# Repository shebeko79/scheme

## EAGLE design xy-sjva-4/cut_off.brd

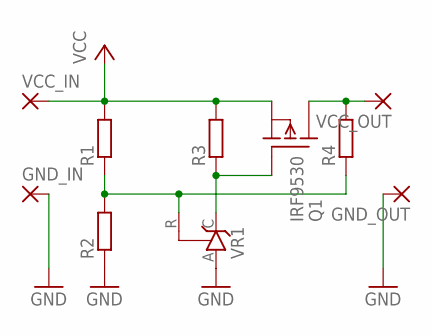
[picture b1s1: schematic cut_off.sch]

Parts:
GND_IN: 2,15/1,0
GND_OUT: 2,15/1,0
Q1: IRF9530; TO220
R1, R2, R3, R4: R-EU_R0805; R0805
VCC_IN: 2,15/1,0
VCC_OUT: 2,15/1,0
VR1: TL431CLP; TO92-CLP

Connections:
GND: GND_IN.1, GND_OUT.1, R2.1, VR1.A
unnamed: R1.1, R2.2, R4.1, VR1.R
unnamed: Q1.1 (G), R3.1, VR1.C
VCC: Q1.3 (S), R1.2, R3.2, VCC_IN.1
VCC_OUT: Q1.2 (D), R4.2, VCC_OUT.1

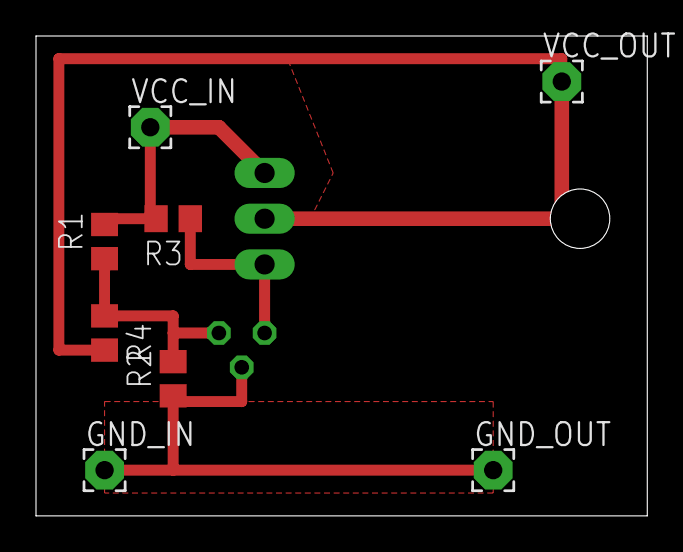
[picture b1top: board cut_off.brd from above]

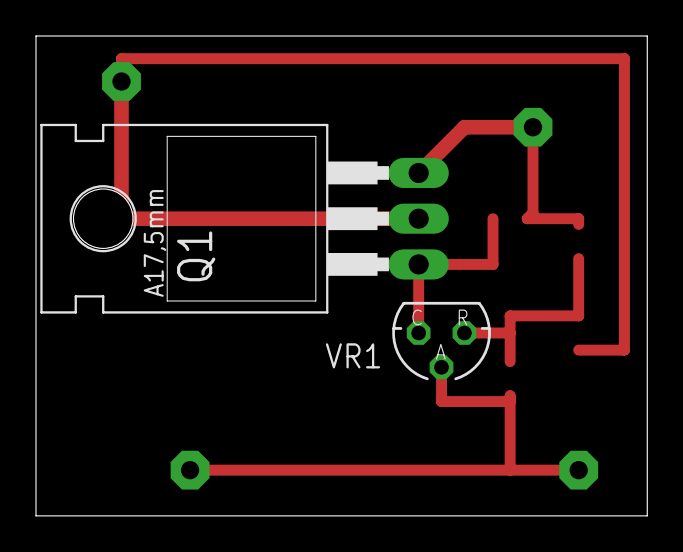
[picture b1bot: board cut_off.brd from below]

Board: 2 copper layers, 34.0 x 26.7 mm, 10 parts (2 on the bottom side), 5 nets.

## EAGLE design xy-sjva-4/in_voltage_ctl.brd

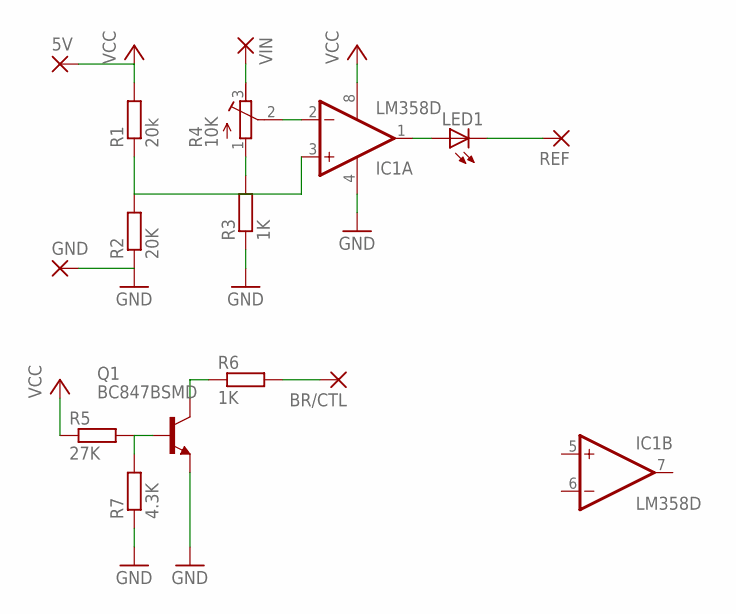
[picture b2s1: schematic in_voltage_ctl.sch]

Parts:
5V: SMD2; SMD1,27-2,54
BR/CTL: SMD2; SMD1,27-2,54
GND: SMD2; SMD1,27-2,54
IC1: LM358D; SO08
LED1: LEDSML0805; SML0805
Q1: BC847BSMD; SOT23
R1: 20k; R0805
R2: 20K; R0805
R3, R6: 1K; R0805
R4: 10K; RTRIM3296W
R5: 27K; R0805
R7: 4.3K; R0805
REF: SMD2; SMD1,27-2,54
VIN: SMD2; SMD1,27-2,54

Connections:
GND: GND.1, IC1.4 (V-), Q1.2 (E), R2.1, R3.1, R7.1
unnamed: IC1.3 (+IN), R1.1, R2.2
unnamed: IC1.1 (OUT), LED1.A
unnamed: LED1.C, REF.1
unnamed: Q1.1 (B), R5.2, R7.2
unnamed: Q1.3 (C), R6.1
unnamed: BR/CTL.1, R6.2
REF: IC1.2 (-IN), R4.2 (S)
REF_GND: R3.2, R4.1 (A)
VCC: 5V.1, IC1.8 (V+), R1.2, R5.1
VIN: R4.3 (E), VIN.1

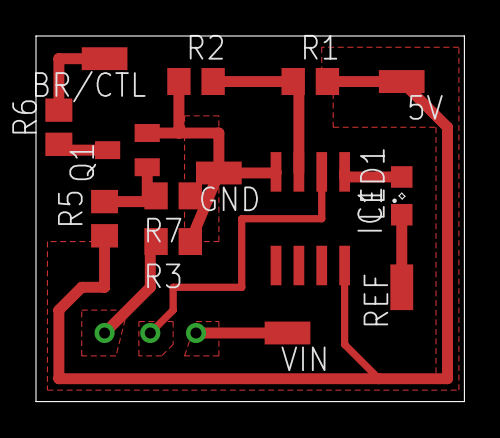
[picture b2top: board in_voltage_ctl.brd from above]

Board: 2 copper layers, 23.8 x 20.3 mm, 15 parts (1 on the bottom side), 11 nets.

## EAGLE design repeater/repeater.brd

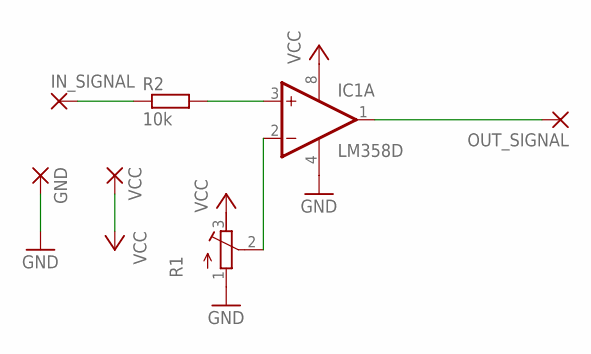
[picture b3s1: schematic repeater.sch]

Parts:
GND: SMD5; SMD2,54-5,08
IC1: LM358D; SO08
IN_SIGNAL: SMD5; SMD2,54-5,08
OUT_SIGNAL: SMD5; SMD2,54-5,08
R1: R-TRIMM3296W; RTRIM3296W
R2: 10k; R0805
VCC: SMD5; SMD2,54-5,08

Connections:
GND: GND.1, IC1.4 (V-), R1.1 (A)
unnamed: IC1.2 (-IN), R1.2 (S)
unnamed: IC1.3 (+IN), R2.2
unnamed: IN_SIGNAL.1, R2.1
unnamed: IC1.1 (OUT), OUT_SIGNAL.1
VCC: IC1.8 (V+), R1.3 (E), VCC.1

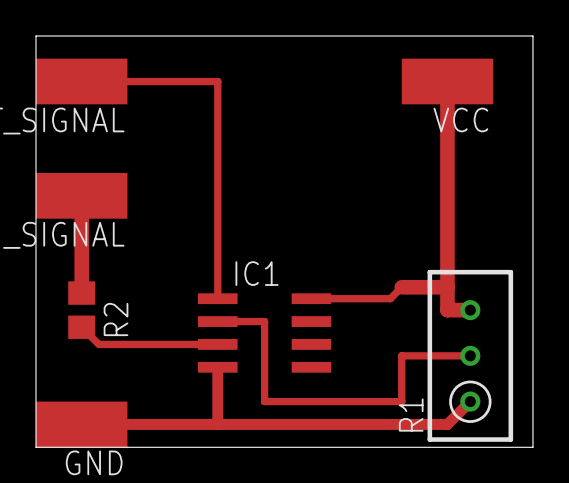
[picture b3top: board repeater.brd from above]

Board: 2 copper layers, 27.6 x 22.9 mm, 7 parts (0 on the bottom side), 6 nets.

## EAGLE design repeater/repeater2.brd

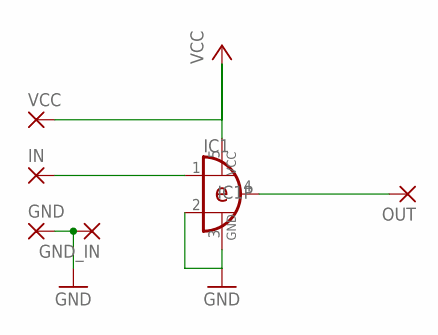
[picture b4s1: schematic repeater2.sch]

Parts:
GND: SMD2; SMD1,27-2,54
GND_IN: SMD2; SMD1,27-2,54
IC1: 74AHC1G86DCK; SC70-5
IN: SMD2; SMD1,27-2,54
OUT: SMD2; SMD1,27-2,54
VCC: SMD2; SMD1,27-2,54

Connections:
GND: GND.1, GND_IN.1, IC1.2 (I1), IC1.3 (GND)
unnamed: IC1.1 (I0), IN.1
unnamed: IC1.4 (O), OUT.1
VCC: IC1.5 (VCC), VCC.1

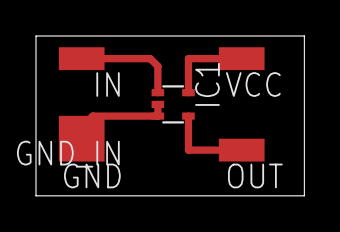
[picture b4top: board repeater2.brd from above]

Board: 2 copper layers, 14.9 x 8.9 mm, 6 parts (0 on the bottom side), 4 nets.

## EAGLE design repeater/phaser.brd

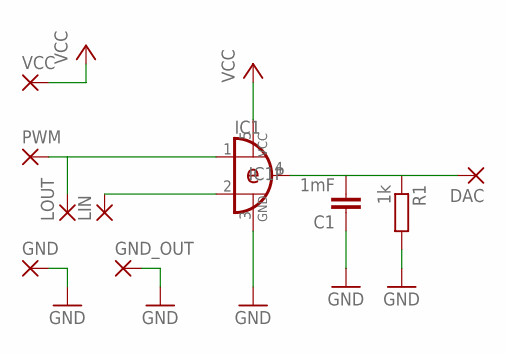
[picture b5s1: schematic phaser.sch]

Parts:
C1: 1mF; C0805
DAC: SMD2; SMD1,27-2,54
GND: SMD2; SMD1,27-2,54
GND_OUT: SMD2; SMD1,27-2,54
IC1: 74AHC1G86DCK; SC70-5
LIN: SMD2; SMD1,27-2,54
LOUT: SMD2; SMD1,27-2,54
PWM: SMD2; SMD1,27-2,54
R1: 1k; R0805
VCC: SMD2; SMD1,27-2,54

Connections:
GND: C1.1, GND.1, GND_OUT.1, IC1.3 (GND), R1.2
unnamed: IC1.1 (I0), LOUT.1, PWM.1
unnamed: IC1.2 (I1), LIN.1
unnamed: C1.2, DAC.1, IC1.4 (O), R1.1
VCC: IC1.5 (VCC), VCC.1

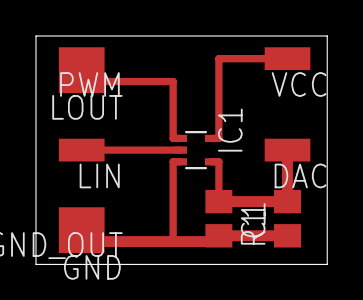
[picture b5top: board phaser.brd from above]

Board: 2 copper layers, 16.2 x 12.7 mm, 10 parts (0 on the bottom side), 5 nets.

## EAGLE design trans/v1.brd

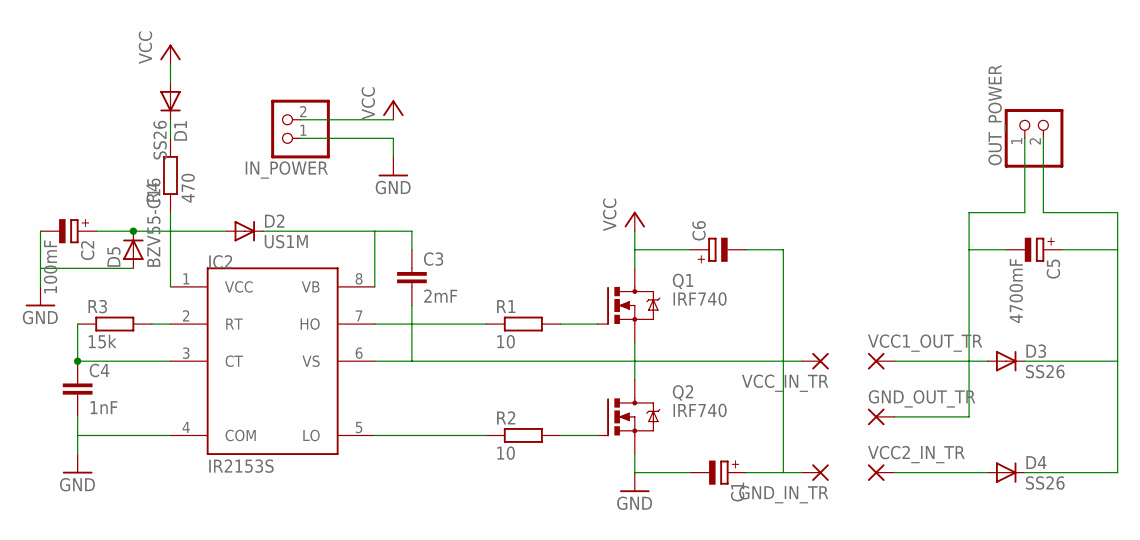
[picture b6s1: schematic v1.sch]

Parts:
C1, C6: CPOL-EUE10-22.5; EB22,5D
C2: 100mF; PANASONIC_C
C3: 2mF; C0805
C4: 1nF; C0805
C5: 4700mF; E7,5-18
D1, D3, D4: SS26; DO-214AC
D2: US1M; DO-214AC
D5: BZV55-C16; SOD80
GND_IN_TR: 1,6/0,8
GND_OUT_TR: 1,6/0,8
IC2: IR2153S; SO08
IN_POWER: PINHD-1X2; 1X02
OUT_POWER: PINHD-1X2; 1X02
Q1, Q2: IRF740; TO220BV
R1, R2: 10; R0805
R3: 15k; R0805
R4: 470; R0805
VCC1_OUT_TR, VCC2_IN_TR: 1,6/0,8
VCC_IN_TR: 1,6/0,8

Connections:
GND: C1.-, C2.-, C4.2, D5.2 (A), IC2.4 (COM), IN_POWER.1, Q2.S
unnamed: IC2.7 (HO), R1.1
unnamed: IC2.5 (LO), R2.1
unnamed: C1.+, C6.-, GND_IN_TR.1
unnamed: Q1.G, R1.2
unnamed: Q2.G, R2.2
unnamed: D3.A, VCC1_OUT_TR.1
unnamed: IC2.2 (RT), R3.2
unnamed: C4.1, IC2.3 (CT), R3.1
unnamed: D4.A, VCC2_IN_TR.1
unnamed: C5.-, GND_OUT_TR.1, OUT_POWER.1
unnamed: C5.+, D3.C, D4.C, OUT_POWER.2
unnamed: D1.C, R4.2
VB: C3.1, D2.C, IC2.8 (VB)
VCC: C6.+, D1.A, IN_POWER.2, Q1.D
VCC_IR: C2.+, D2.A, D5.1 (C), IC2.1 (VCC), R4.1
VS: C3.2, IC2.6 (VS), Q1.S, Q2.D, VCC_IN_TR.1

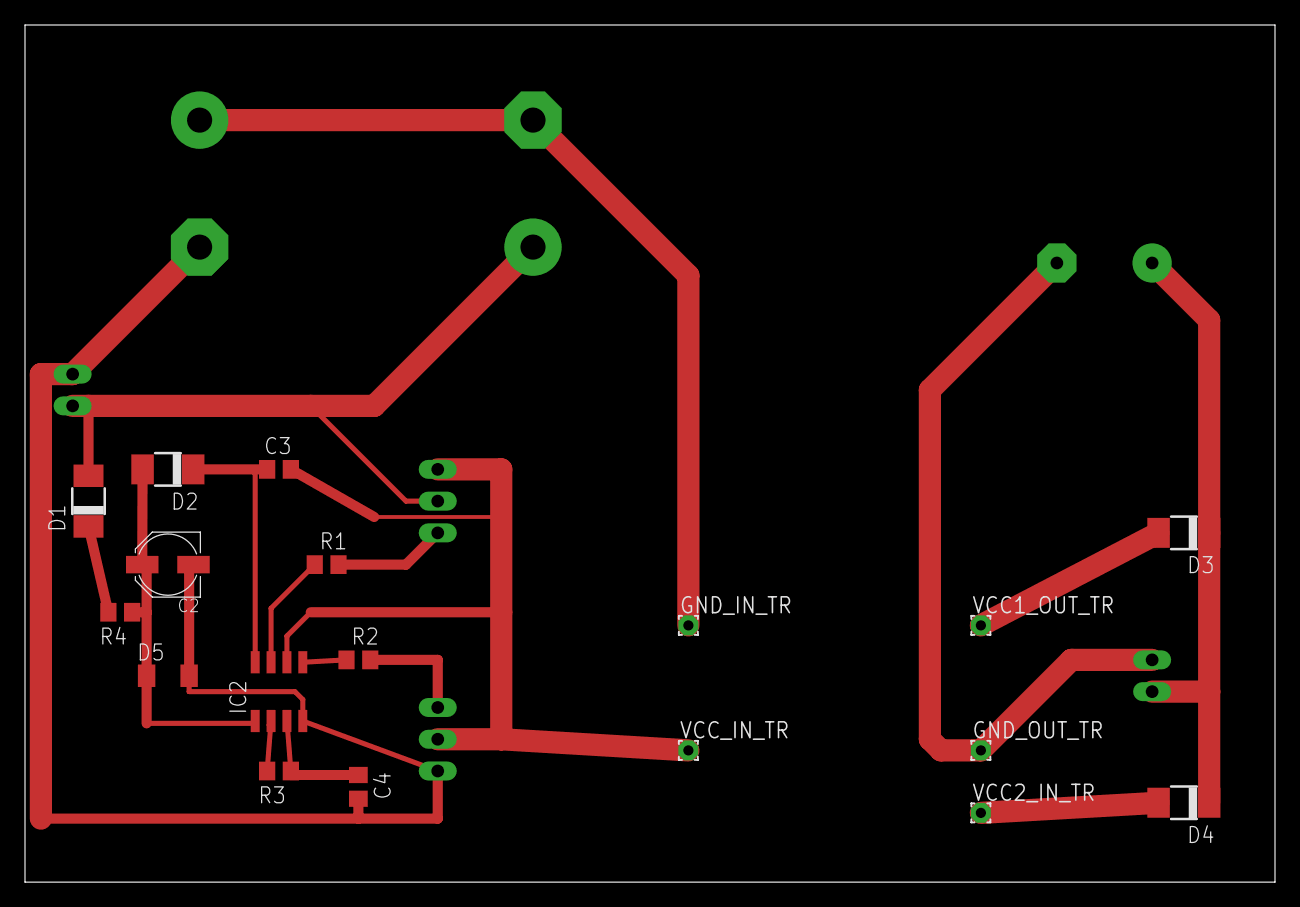
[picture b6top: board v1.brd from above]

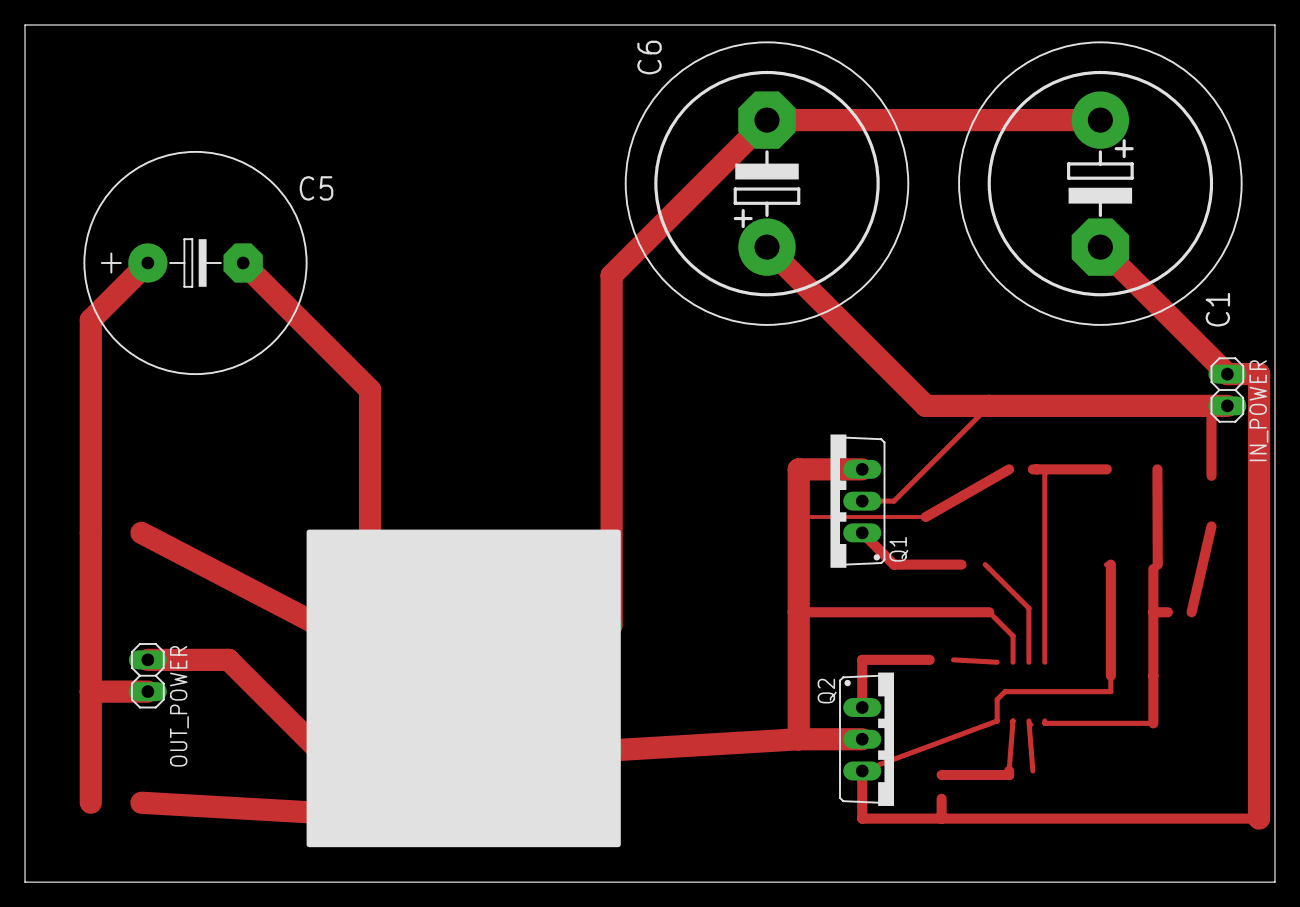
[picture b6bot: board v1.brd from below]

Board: 2 copper layers, 100.0 x 68.6 mm, 25 parts (7 on the bottom side), 17 nets.

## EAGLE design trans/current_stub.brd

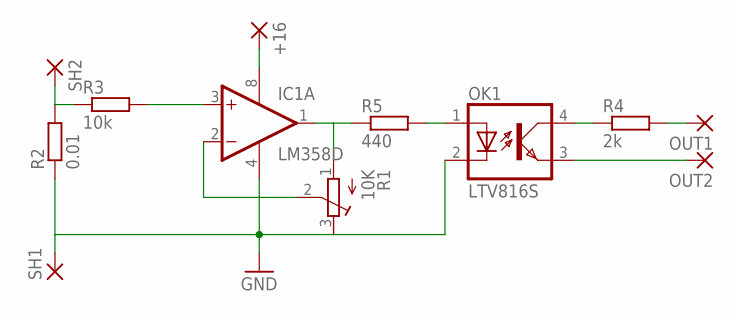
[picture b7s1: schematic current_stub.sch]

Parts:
+16: SMD2; SMD1,27-2,54
IC1: LM358D; SO08
OK1: LTV816S; SMD4
OUT1, OUT2: SMD2; SMD1,27-2,54
R1: 10K; RTRIM3296W
R2: 0.01; R2512
R3: 10k; M0805
R4: 2k; M0805
R5: 440; M0805
SH1, SH2: SMD2; SMD1,27-2,54

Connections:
GND: IC1.4 (V-), OK1.2 (C), R1.3 (E), R2.1, SH1.1
unnamed: IC1.3 (+IN), R3.2
unnamed: R2.2, R3.1, SH2.1
unnamed: IC1.2 (-IN), R1.2 (S)
unnamed: +16.1, IC1.8 (V+)
unnamed: IC1.1 (OUT), R1.1 (A), R5.1
unnamed: OK1.1 (A), R5.2
unnamed: OK1.4 (COL), R4.1
unnamed: OUT1.1, R4.2
OUT2: OK1.3 (EMIT), OUT2.1

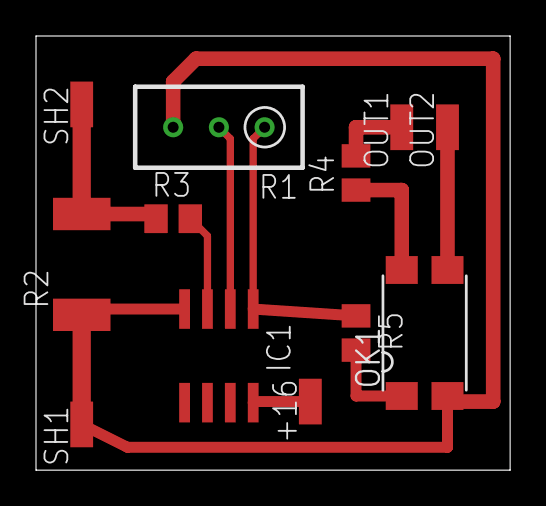
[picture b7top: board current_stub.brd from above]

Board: 2 copper layers, 26.3 x 24.1 mm, 12 parts (0 on the bottom side), 10 nets.

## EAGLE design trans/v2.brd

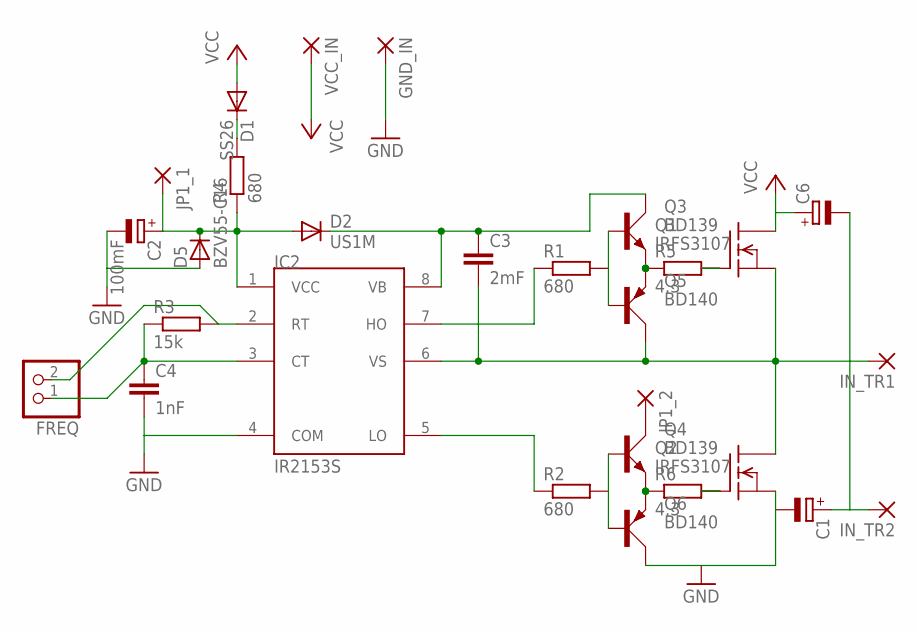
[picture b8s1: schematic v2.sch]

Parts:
C1, C6: CPOL-EUE10-22.5; EB22,5D
C2: 100mF; E5-10,5
C3: 2mF; C0805
C4: 1nF; C0805
D1: SS26; DO-214AC
D2: US1M; DO-214AC
D5: BZV55-C16; SOD80
FREQ: PINHD-1X2/90; 1X02/90
GND_IN: SMD5; SMD2,54-5,08
IC2: IR2153S; SO08
IN_TR1, IN_TR2: SMD5; SMD2,54-5,08
JP1_1, JP1_2: 1,6/0,8
Q1, Q2: IRFS3107; D2PAK
Q3, Q4: BD139; TO126AV
Q5, Q6: BD140; TO126AV
R1, R2, R4: 680; R0805
R3: 15k; R0805
R5, R6: 4.3; R0805
VCC_IN: SMD5; SMD2,54-5,08

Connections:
GND: C1.-, C2.-, C4.2, D5.2 (A), GND_IN.1, IC2.4 (COM), Q2.3 (S), Q6.C
IN_TR1: C3.2, IC2.6 (VS), IN_TR1.1, Q1.3 (S), Q2.2 (D), Q5.C
IN_TR2: C1.+, C6.-, IN_TR2.1
unnamed: Q3.B, Q5.B, R1.2
unnamed: Q4.B, Q6.B, R2.2
unnamed: Q3.E, Q5.E, R5.1
unnamed: Q4.E, Q6.E, R6.1
unnamed: Q1.1 (G), R5.2
unnamed: FREQ.2, IC2.2 (RT), R3.2
unnamed: C4.1, FREQ.1, IC2.3 (CT), R3.1
unnamed: Q2.1 (G), R6.2
unnamed: IC2.7 (HO), R1.1
unnamed: IC2.5 (LO), R2.1
unnamed: D1.C, R4.2
unnamed: JP1_2.1, Q4.C
VB: C3.1, D2.C, IC2.8 (VB), Q3.C
VCC: C6.+, D1.A, Q1.2 (D), VCC_IN.1
VCC_IR: C2.+, D2.A, D5.1 (C), IC2.1 (VCC), JP1_1.1, R4.1

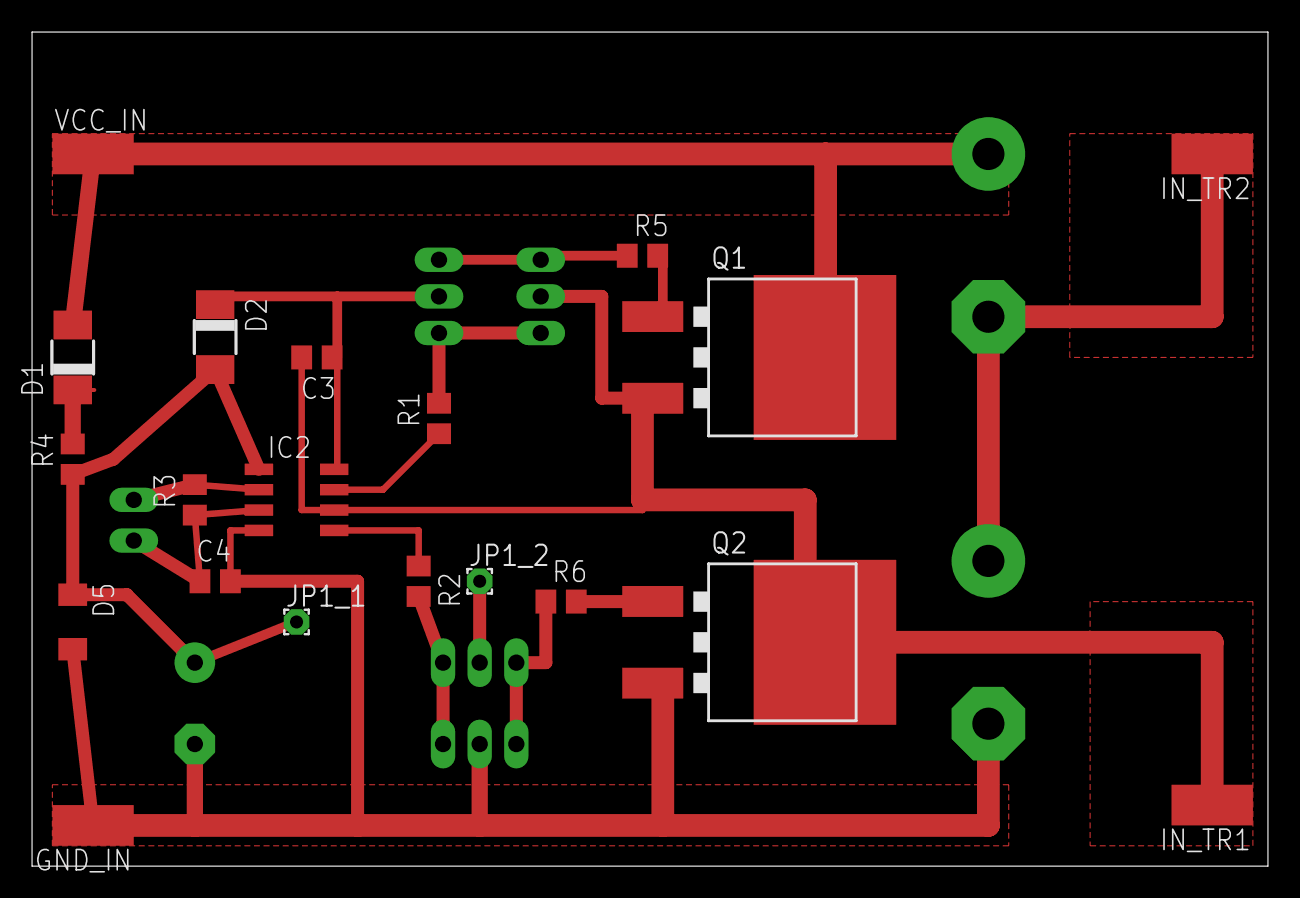
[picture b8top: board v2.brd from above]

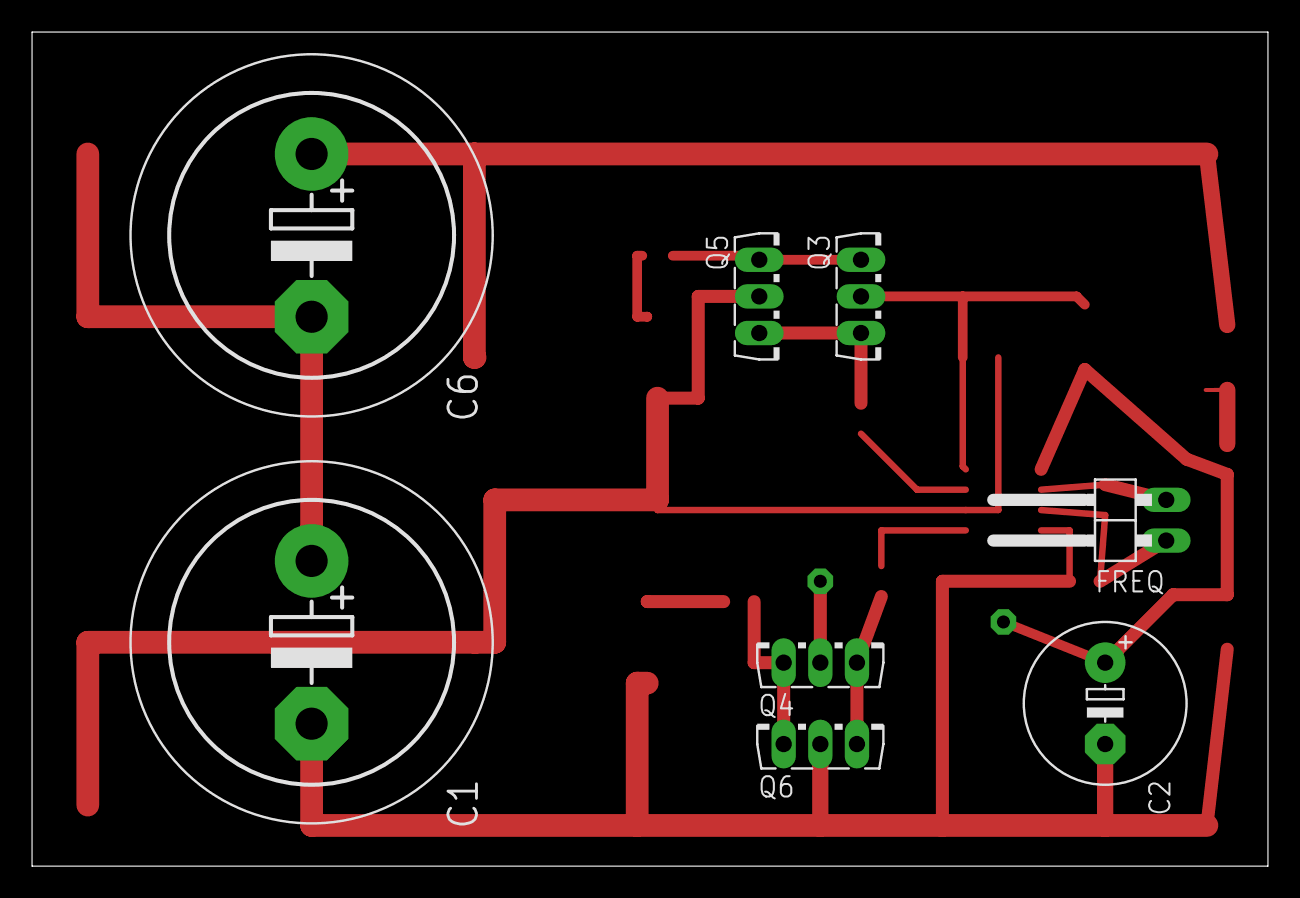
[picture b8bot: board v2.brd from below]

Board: 2 copper layers, 77.1 x 52.1 mm, 28 parts (8 on the bottom side), 18 nets.

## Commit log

2023-01-16 add gitignore
2023-01-16 libraries files
2023-01-16 Optopair module with common ground. Just the way to open 12v transistor from 3.3v microcontroller line
2023-01-16 Just a big key with few mossfet and mossfet driver on pnp npn transistors
2023-01-16 Tried to implement spot welding. ESP32 works as NE555 timer. Separate power buffer for ESP32. EL817 optopair onboard to control key form power scheme.
2023-01-16 All project around 18-30V DC to 4.2 V DC half-bridge IR2153 convertor
2023-01-16 Exclude gereber folders
2023-01-16 TOF for poor All projects to test Derek's video https://www.youtube.com/watch?v=oI_X2cMHNe0
2025-08-27 How to make (almost) MPPT from XY-SJVA-4 XY-SJVA-4 CC/CV controller has maximum current protection. And it stuck in this protection mode whenever sun disappear and input voltage drops. Which make pra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
